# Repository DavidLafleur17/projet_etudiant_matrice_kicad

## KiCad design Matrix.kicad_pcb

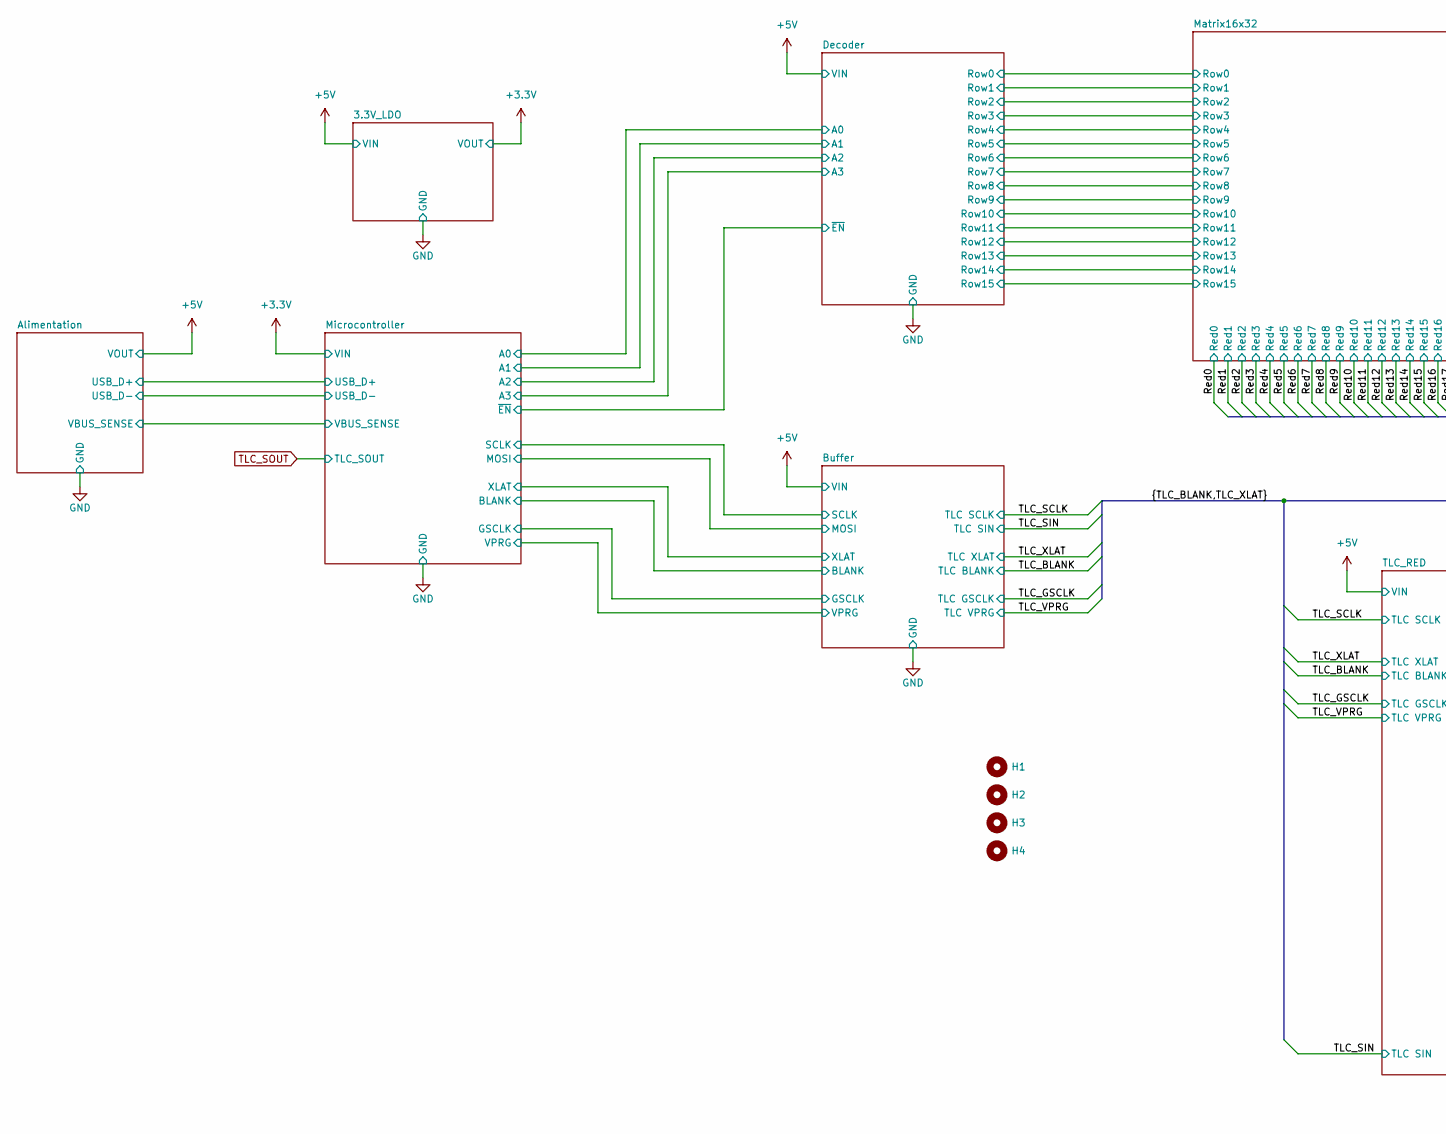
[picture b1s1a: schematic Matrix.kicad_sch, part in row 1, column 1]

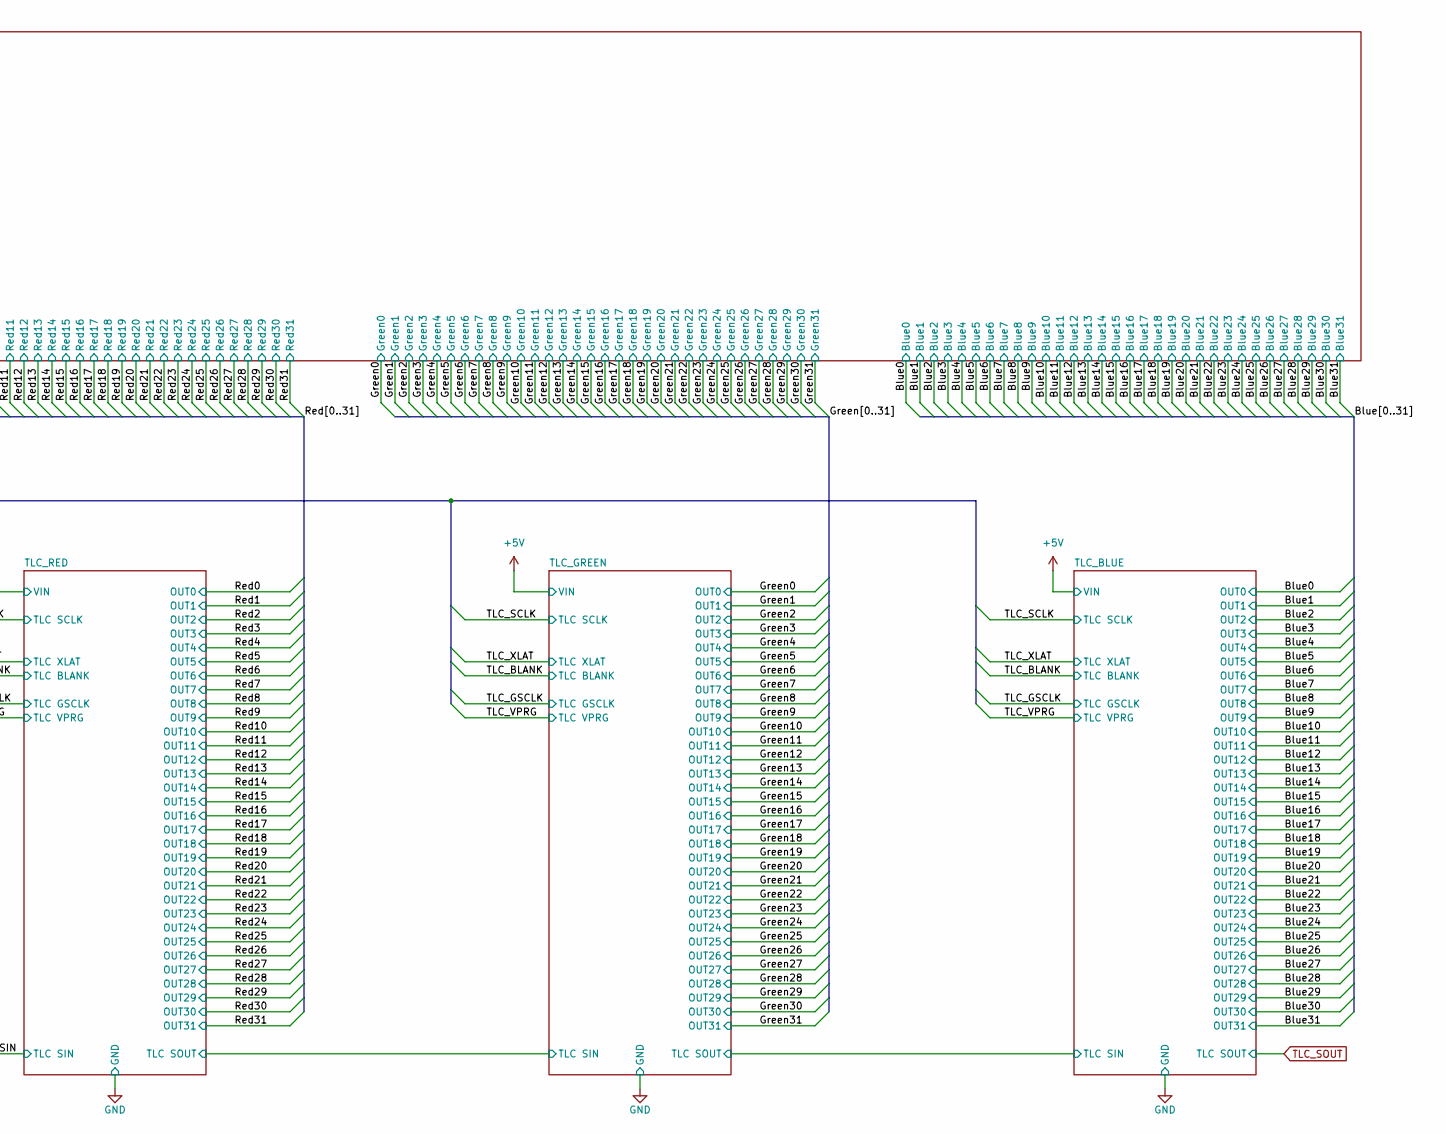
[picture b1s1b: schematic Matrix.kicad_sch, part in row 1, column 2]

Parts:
H1, H2, H3, H4: MountingHole; MountingHole_3mm

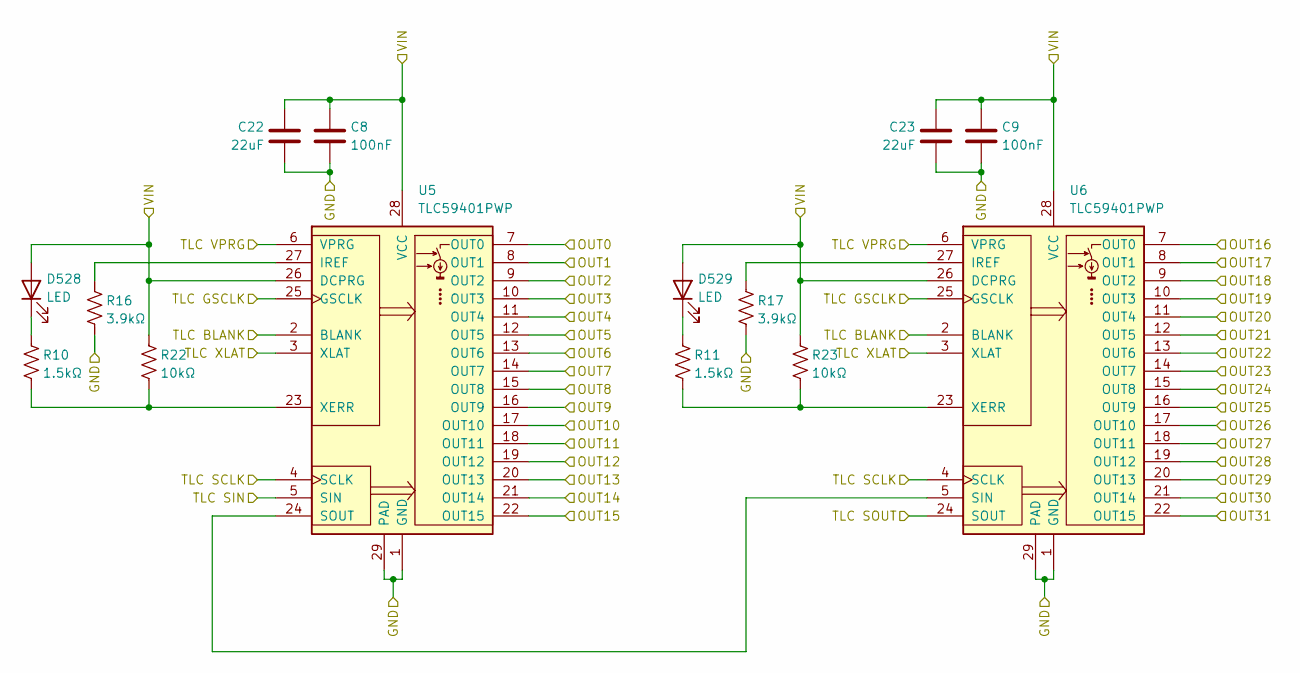
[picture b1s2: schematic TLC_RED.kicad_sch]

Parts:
C8, C9: 100nF; C_0805_2012Metric_Pad1.18x1.45mm_HandSolder; DigiKey PN 399-C0805F104K1RACAUTOCT-ND
C22, C23: 22uF; C_0805_2012Metric_Pad1.18x1.45mm_HandSolder; DigiKey PN 1276-CL21A226MAYNNNECT-ND
D528, D529: LED; LED_0805_2012Metric_Pad1.15x1.40mm_HandSolder; DigiKey PN 475-LSR976-NR-1CT-ND
R10, R11: 1.5kΩ; R_0805_2012Metric_Pad1.20x1.40mm_HandSolder; DigiKey PN 2019-RK73H2ATTD1501FCT-ND
R16, R17: 3.9kΩ; R_0805_2012Metric_Pad1.20x1.40mm_HandSolder; DigiKey PN 2019-RK73H2ATTD3901FCT-ND
R22, R23: 10kΩ; R_0805_2012Metric_Pad1.20x1.40mm_HandSolder; DigiKey PN 2019-RK73H2ATTD1002FCT-ND
U5, U6: TLC59401PWP; HTSSOP-28-1EP_4.4x9.7mm_P0.65mm_EP3.4x9.5mm_Mask2.4x6.17mm_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; DigiKey PN 296-25565-1-ND

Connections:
+5V: C8.1, C9.1, C22.1, C23.1, D528.2 (A), D529.2 (A), R22.1, R23.1, U5.26 (DCPRG), U5.28 (VCC), U6.26 (DCPRG), U6.28 (VCC); also elsewhere on the board
/Red0: U5.7 (OUT0); also elsewhere on the board
/Red1: U5.8 (OUT1); also elsewhere on the board
/Red2: U5.9 (OUT2); also elsewhere on the board
/Red3: U5.10 (OUT3); also elsewhere on the board
/Red4: U5.11 (OUT4); also elsewhere on the board
/Red5: U5.12 (OUT5); also elsewhere on the board
/Red6: U5.13 (OUT6); also elsewhere on the board
/Red7: U5.14 (OUT7); also elsewhere on the board
/Red8: U5.15 (OUT8); also elsewhere on the board
/Red9: U5.16 (OUT9); also elsewhere on the board
/Red10: U5.17 (OUT10); also elsewhere on the board
/Red11: U5.18 (OUT11); also elsewhere on the board
/Red12: U5.19 (OUT12); also elsewhere on the board
/Red13: U5.20 (OUT13); also elsewhere on the board
/Red14: U5.21 (OUT14); also elsewhere on the board
/Red15: U5.22 (OUT15); also elsewhere on the board
/Red16: U6.7 (OUT0); also elsewhere on the board
/Red17: U6.8 (OUT1); also elsewhere on the board
/Red18: U6.9 (OUT2); also elsewhere on the board
/Red19: U6.10 (OUT3); also elsewhere on the board
/Red20: U6.11 (OUT4); also elsewhere on the board
/Red21: U6.12 (OUT5); also elsewhere on the board
/Red22: U6.13 (OUT6); also elsewhere on the board
/Red23: U6.14 (OUT7); also elsewhere on the board
/Red24: U6.15 (OUT8); also elsewhere on the board
/Red25: U6.16 (OUT9); also elsewhere on the board
/Red26: U6.17 (OUT10); also elsewhere on the board
/Red27: U6.18 (OUT11); also elsewhere on the board
/Red28: U6.19 (OUT12); also elsewhere on the board
/Red29: U6.20 (OUT13); also elsewhere on the board
/Red30: U6.21 (OUT14); also elsewhere on the board
/Red31: U6.22 (OUT15); also elsewhere on the board
/TLC_BLANK: U5.2 (BLANK), U6.2 (BLANK); also elsewhere on the board
/TLC_GREEN/TLC SIN: U6.24 (SOUT); also elsewhere on the board
/TLC_GSCLK: U5.25 (GSCLK), U6.25 (GSCLK); also elsewhere on the board
/TLC_SCLK: U5.4 (SCLK), U6.4 (SCLK); also elsewhere on the board
/TLC_SIN: U5.5 (SIN); also elsewhere on the board
/TLC_VPRG: U5.6 (VPRG), U6.6 (VPRG); also elsewhere on the board
/TLC_XLAT: U5.3 (XLAT), U6.3 (XLAT); also elsewhere on the board
GND: C8.2, C9.2, C22.2, C23.2, R16.2, R17.2, U5.1 (GND), U5.29 (PAD), U6.1 (GND), U6.29 (PAD); also elsewhere on the board
unnamed: D528.1 (K), R10.1
unnamed: D529.1 (K), R11.1
unnamed: R16.1, U5.27 (IREF)
unnamed: U5.24 (SOUT), U6.5 (SIN)
unnamed: R10.2, R22.2, U5.23 (XERR)
unnamed: R17.1, U6.27 (IREF)
unnamed: R11.2, R23.2, U6.23 (XERR)

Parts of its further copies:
C10, C11, C12, C13: 100nF; C_0805_2012Metric_Pad1.18x1.45mm_HandSolder; DigiKey PN 399-C0805F104K1RACAUTOCT-ND
C24, C25, C26, C27: 22uF; C_0805_2012Metric_Pad1.18x1.45mm_HandSolder; DigiKey PN 1276-CL21A226MAYNNNECT-ND
D530, D531, D532, D533: LED; LED_0805_2012Metric_Pad1.15x1.40mm_HandSolder; DigiKey PN 475-LSR976-NR-1CT-ND
R12, R13, R14, R15: 1.5kΩ; R_0805_2012Metric_Pad1.20x1.40mm_HandSolder; DigiKey PN 2019-RK73H2ATTD1501FCT-ND
R18, R19, R20, R21: 3.9kΩ; R_0805_2012Metric_Pad1.20x1.40mm_HandSolder; DigiKey PN 2019-RK73H2ATTD3901FCT-ND
R24, R25, R26, R27: 10kΩ; R_0805_2012Metric_Pad1.20x1.40mm_HandSolder; DigiKey PN 2019-RK73H2ATTD1002FCT-ND

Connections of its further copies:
+5V: C10.1, C11.1, C12.1, C13.1, C24.1, C25.1, C26.1, C27.1, D530.2 (A), D531.2 (A), D532.2 (A), D533.2 (A), R24.1, R25.1, R26.1, R27.1; also elsewhere on the board
GND: C10.2, C11.2, C12.2, C13.2, C24.2, C25.2, C26.2, C27.2, R18.2, R19.2, R20.2, R21.2; also elsewhere on the board
unnamed: D530.1 (K), R12.1
unnamed: D531.1 (K), R13.1
unnamed: D532.1 (K), R14.1
unnamed: D533.1 (K), R15.1
unnamed 188: R18.1; also elsewhere on the board
unnamed 190: R12.2, R24.2; also elsewhere on the board
unnamed 191: R19.1; also elsewhere on the board
unnamed 192: R13.2, R25.2; also elsewhere on the board
unnamed 193: R20.1; also elsewhere on the board
unnamed 194: R14.2, R26.2; also elsewhere on the board
unnamed 195: R21.1; also elsewhere on the board
unnamed 197: R15.2, R27.2; also elsewhere on the board

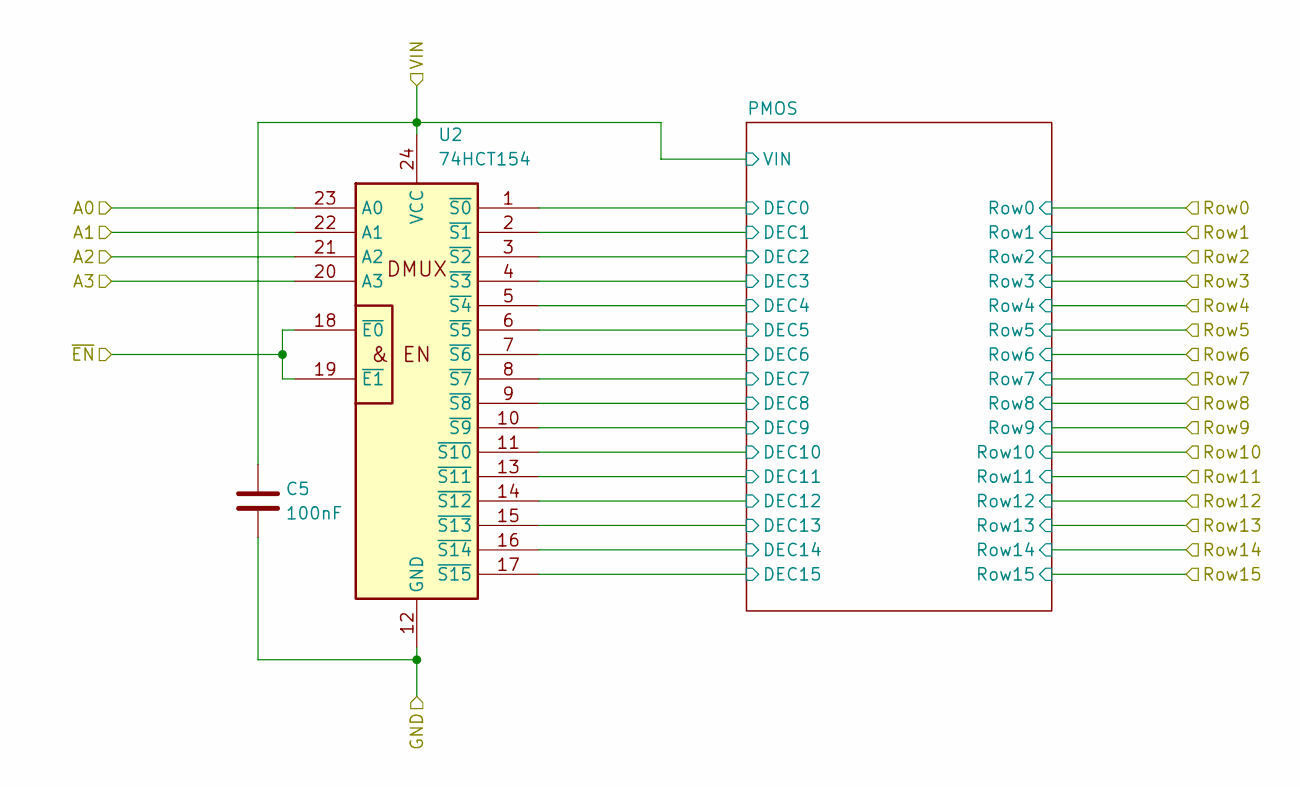
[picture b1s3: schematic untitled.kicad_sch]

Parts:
C5: 100nF; C_0805_2012Metric_Pad1.18x1.45mm_HandSolder; DigiKey PN 399-C0805F104K1RACAUTOCT-ND
U2: 74HCT154; SOIC-24W_7.5x15.4mm_P1.27mm; DigiKey PN 296-31604-1-ND

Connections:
+5V: C5.1, U2.24 (VCC); also elsewhere on the board
/Decoder/A0: U2.23 (A0); also elsewhere on the board
/Decoder/A1: U2.22 (A1); also elsewhere on the board
/Decoder/A2: U2.21 (A2); also elsewhere on the board
/Decoder/A3: U2.20 (A3); also elsewhere on the board
/Decoder/PMOS/DEC0: U2.1 (~S0); also elsewhere on the board
/Decoder/PMOS/DEC1: U2.2 (~S1); also elsewhere on the board
/Decoder/PMOS/DEC2: U2.3 (~S2); also elsewhere on the board
/Decoder/PMOS/DEC3: U2.4 (~S3); also elsewhere on the board
/Decoder/PMOS/DEC4: U2.5 (~S4); also elsewhere on the board
/Decoder/PMOS/DEC5: U2.6 (~S5); also elsewhere on the board
/Decoder/PMOS/DEC6: U2.7 (~S6); also elsewhere on the board
/Decoder/PMOS/DEC7: U2.8 (~S7); also elsewhere on the board
/Decoder/PMOS/DEC8: U2.9 (~S8); also elsewhere on the board
/Decoder/PMOS/DEC9: U2.10 (~S9); also elsewhere on the board
/Decoder/PMOS/DEC10: U2.11 (~S10); also elsewhere on the board
/Decoder/PMOS/DEC11: U2.13 (~S11); also elsewhere on the board
/Decoder/PMOS/DEC12: U2.14 (~S12); also elsewhere on the board
/Decoder/PMOS/DEC13: U2.15 (~S13); also elsewhere on the board
/Decoder/PMOS/DEC14: U2.16 (~S14); also elsewhere on the board
/Decoder/PMOS/DEC15: U2.17 (~S15); also elsewhere on the board
/Decoder/~EN: U2.18 (~E0), U2.19 (~E1); also elsewhere on the board
GND: C5.2, U2.12 (GND); also elsewhere on the board

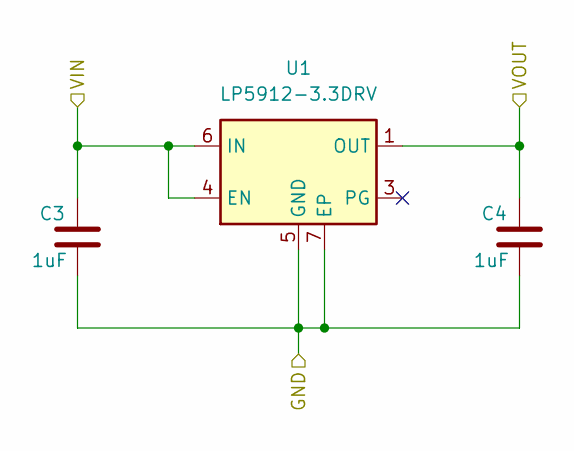
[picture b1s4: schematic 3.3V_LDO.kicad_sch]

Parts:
C3, C4: 1uF; C_0805_2012Metric_Pad1.18x1.45mm_HandSolder; DigiKey PN 1276-6469-1-ND
U1: LP5912-3.3DRV; WSON-6-1EP_2x2mm_P0.65mm_EP1x1.6mm_ThermalVias; DigiKey PN 296-47214-1-ND

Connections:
+3.3V: C4.1, U1.1 (OUT); also elsewhere on the board
+5V: C3.1, U1.4 (EN), U1.6 (IN); also elsewhere on the board
GND: C3.2, C4.2, U1.5 (GND), U1.7 (EP); also elsewhere on the board

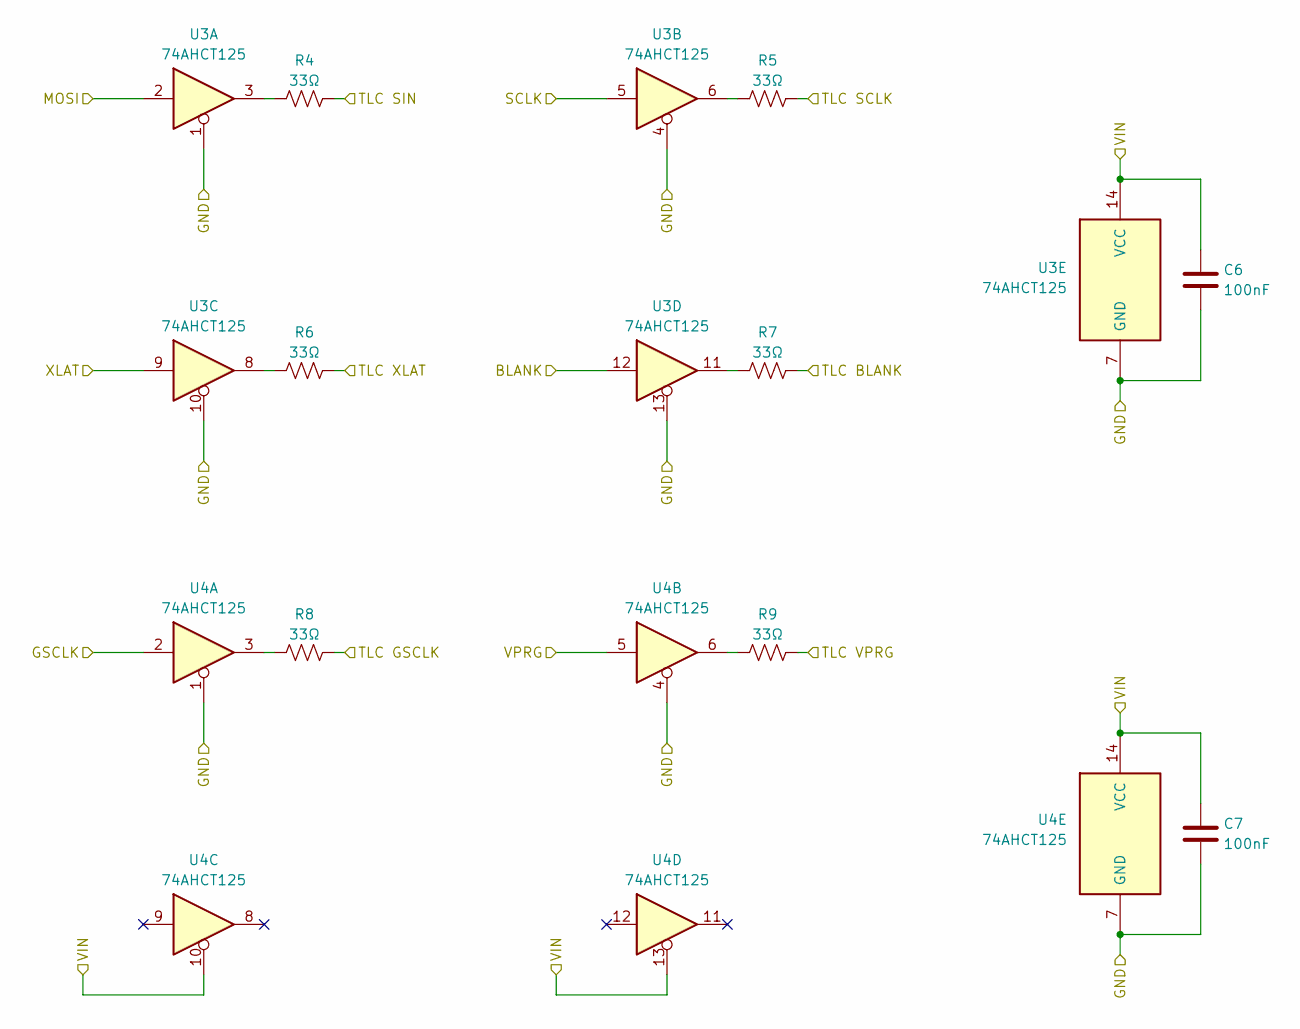
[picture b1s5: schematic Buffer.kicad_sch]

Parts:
C6, C7: 100nF; C_0805_2012Metric_Pad1.18x1.45mm_HandSolder; DigiKey PN 399-C0805F104K1RACAUTOCT-ND
R4, R5, R6, R7, R8, R9: 33Ω; R_0805_2012Metric_Pad1.20x1.40mm_HandSolder; DigiKey PN 2019-RK73H2ATTD33R0FCT-ND
U3, U4: 74AHCT125; SO-14_3.9x8.65mm_P1.27mm; DigiKey PN 31-74AHCT125S14-13CT-ND

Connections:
+5V: C6.1, C7.1, U3.14 (VCC), U4.10, U4.13, U4.14 (VCC); also elsewhere on the board
/Buffer/BLANK: U3.12; also elsewhere on the board
/Buffer/GSCLK: U4.2; also elsewhere on the board
/Buffer/MOSI: U3.2; also elsewhere on the board
/Buffer/SCLK: U3.5; also elsewhere on the board
/Buffer/VPRG: U4.5; also elsewhere on the board
/Buffer/XLAT: U3.9; also elsewhere on the board
/TLC_BLANK: R7.2; also elsewhere on the board
/TLC_GSCLK: R8.2; also elsewhere on the board
/TLC_SCLK: R5.2; also elsewhere on the board
/TLC_SIN: R4.2; also elsewhere on the board
/TLC_VPRG: R9.2; also elsewhere on the board
/TLC_XLAT: R6.2; also elsewhere on the board
GND: C6.2, C7.2, U3.1, U3.4, U3.7 (GND), U3.10, U3.13, U4.1, U4.4, U4.7 (GND); also elsewhere on the board
unnamed: R4.1, U3.3
unnamed: R5.1, U3.6
unnamed: R6.1, U3.8
unnamed: R7.1, U3.11
unnamed: R8.1, U4.3
unnamed: R9.1, U4.6

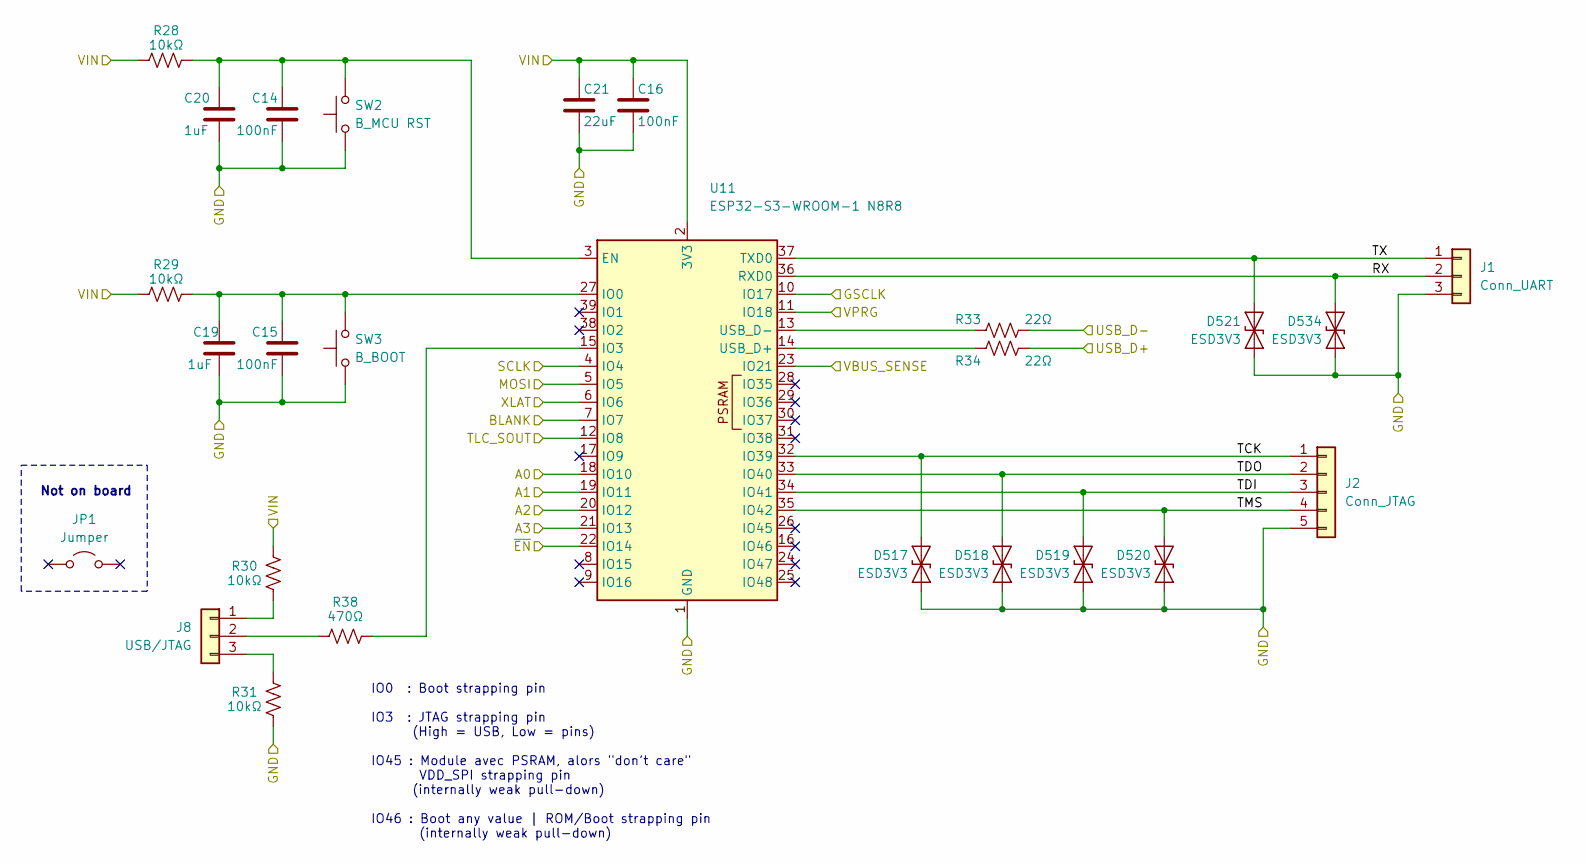
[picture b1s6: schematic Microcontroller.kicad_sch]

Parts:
C14, C15, C16: 100nF; C_0805_2012Metric_Pad1.18x1.45mm_HandSolder; DigiKey PN 399-C0805F104K1RACAUTOCT-ND
C19, C20: 1uF; C_0805_2012Metric_Pad1.18x1.45mm_HandSolder; DigiKey PN 1276-6469-1-ND
C21: 22uF; C_0805_2012Metric_Pad1.18x1.45mm_HandSolder; DigiKey PN 1276-CL21A226MAYNNNECT-ND
D517, D518, D519, D520, D521, D534: ESD3V3; D_0603_1608Metric_Pad1.05x0.95mm_HandSolder; DigiKey PN 31-D3V3S1U2LP1610-7CT-ND
J1: Conn_UART; PinHeader_1x03_P2.54mm_Vertical; DigiKey PN S7036-ND
J2: Conn_JTAG; PinHeader_1x05_P2.54mm_Vertical; DigiKey PN S7038-ND
J8: USB/JTAG; PinHeader_1x03_P2.54mm_Vertical; DigiKey PN 664-G800W305018EU-ND
JP1: Jumper; DigiKey PN S9337-ND
R28, R29, R30, R31: 10kΩ; R_0805_2012Metric_Pad1.20x1.40mm_HandSolder; DigiKey PN 2019-RK73H2ATTD1002FCT-ND
R33, R34: 22Ω; R_0805_2012Metric_Pad1.20x1.40mm_HandSolder; DigiKey PN 2019-RK73H2ATTD22R0FCT-ND
R38: 470Ω; R_0805_2012Metric_Pad1.20x1.40mm_HandSolder; DigiKey PN 2019-RK73H2ATTD4700FCT-ND
SW2: B_MCU RST; SW_Push_1P1T_NO_E-Switch_TL3301NxxxxxG; DigiKey PN 2073-SWT0310-043025GSACT-ND
SW3: B_BOOT; SW_Push_1P1T_NO_E-Switch_TL3301NxxxxxG; DigiKey PN 2073-SWT0310-043025GSACT-ND
U11: ESP32-S3-WROOM-1 N8R8; ESP32-S3-WROOM-1; DigiKey PN 5407-ESP32-S3-WROOM-1-N8R8CT-ND

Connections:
+3.3V: C16.1, C21.1, R28.2, R29.2, R30.1, U11.2 (3V3); also elsewhere on the board
/Alimentation/USB_D+: R34.2; also elsewhere on the board
/Alimentation/USB_D-: R33.2; also elsewhere on the board
/Alimentation/VBUS_SENSE: U11.23 (IO21); also elsewhere on the board
/Buffer/BLANK: U11.7 (IO7); also elsewhere on the board
/Buffer/GSCLK: U11.10 (IO17); also elsewhere on the board
/Buffer/MOSI: U11.5 (IO5); also elsewhere on the board
/Buffer/SCLK: U11.4 (IO4); also elsewhere on the board
/Buffer/VPRG: U11.11 (IO18); also elsewhere on the board
/Buffer/XLAT: U11.6 (IO6); also elsewhere on the board
/Decoder/A0: U11.18 (IO10); also elsewhere on the board
/Decoder/A1: U11.19 (IO11); also elsewhere on the board
/Decoder/A2: U11.20 (IO12); also elsewhere on the board
/Decoder/A3: U11.21 (IO13); also elsewhere on the board
/Decoder/~EN: U11.22 (IO14); also elsewhere on the board
/Microcontroller/RX: D534.1 (A1), J1.2, U11.36 (RXD0)
/Microcontroller/TCK: D517.1 (A1), J2.1, U11.32 (IO39)
/Microcontroller/TDI: D519.1 (A1), J2.3, U11.34 (IO41)
/Microcontroller/TDO: D518.1 (A1), J2.2, U11.33 (IO40)
/Microcontroller/TMS: D520.1 (A1), J2.4, U11.35 (IO42)
/Microcontroller/TX: D521.1 (A1), J1.1, U11.37 (TXD0)
GND: C14.2, C15.2, C16.2, C19.2, C20.2, C21.2, D517.2 (A2), D518.2 (A2), D519.2 (A2), D520.2 (A2), D521.2 (A2), D534.2 (A2), J1.3, J2.5, R31.2, SW2.1, SW3.1, U11.1 (GND), U11.40 (GND), U11.41 (GND); also elsewhere on the board
unnamed: J8.1, R30.2
unnamed: J8.2, R38.1
unnamed: J8.3, R31.1
unnamed: C14.1, C20.1, R28.1, SW2.2, U11.3 (EN)
unnamed: C15.1, C19.1, R29.1, SW3.2, U11.27 (IO0)
unnamed: R38.2, U11.15 (IO3)
unnamed: R34.1, U11.14 (USB_D+)
unnamed: R33.1, U11.13 (USB_D-)
TLC_SOUT: U11.12 (IO8); also elsewhere on the board

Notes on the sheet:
IO0 : Boot strapping pin IO3 : JTAG strapping pin (High = USB, Low = pins) IO45 : Module avec PSRAM, alors "don't care" VDD_SPI strapping pin (internally weak pull-down) IO46 : Boot any value | ROM/Boot strapping pin (internally weak pull-down)
Not on board
